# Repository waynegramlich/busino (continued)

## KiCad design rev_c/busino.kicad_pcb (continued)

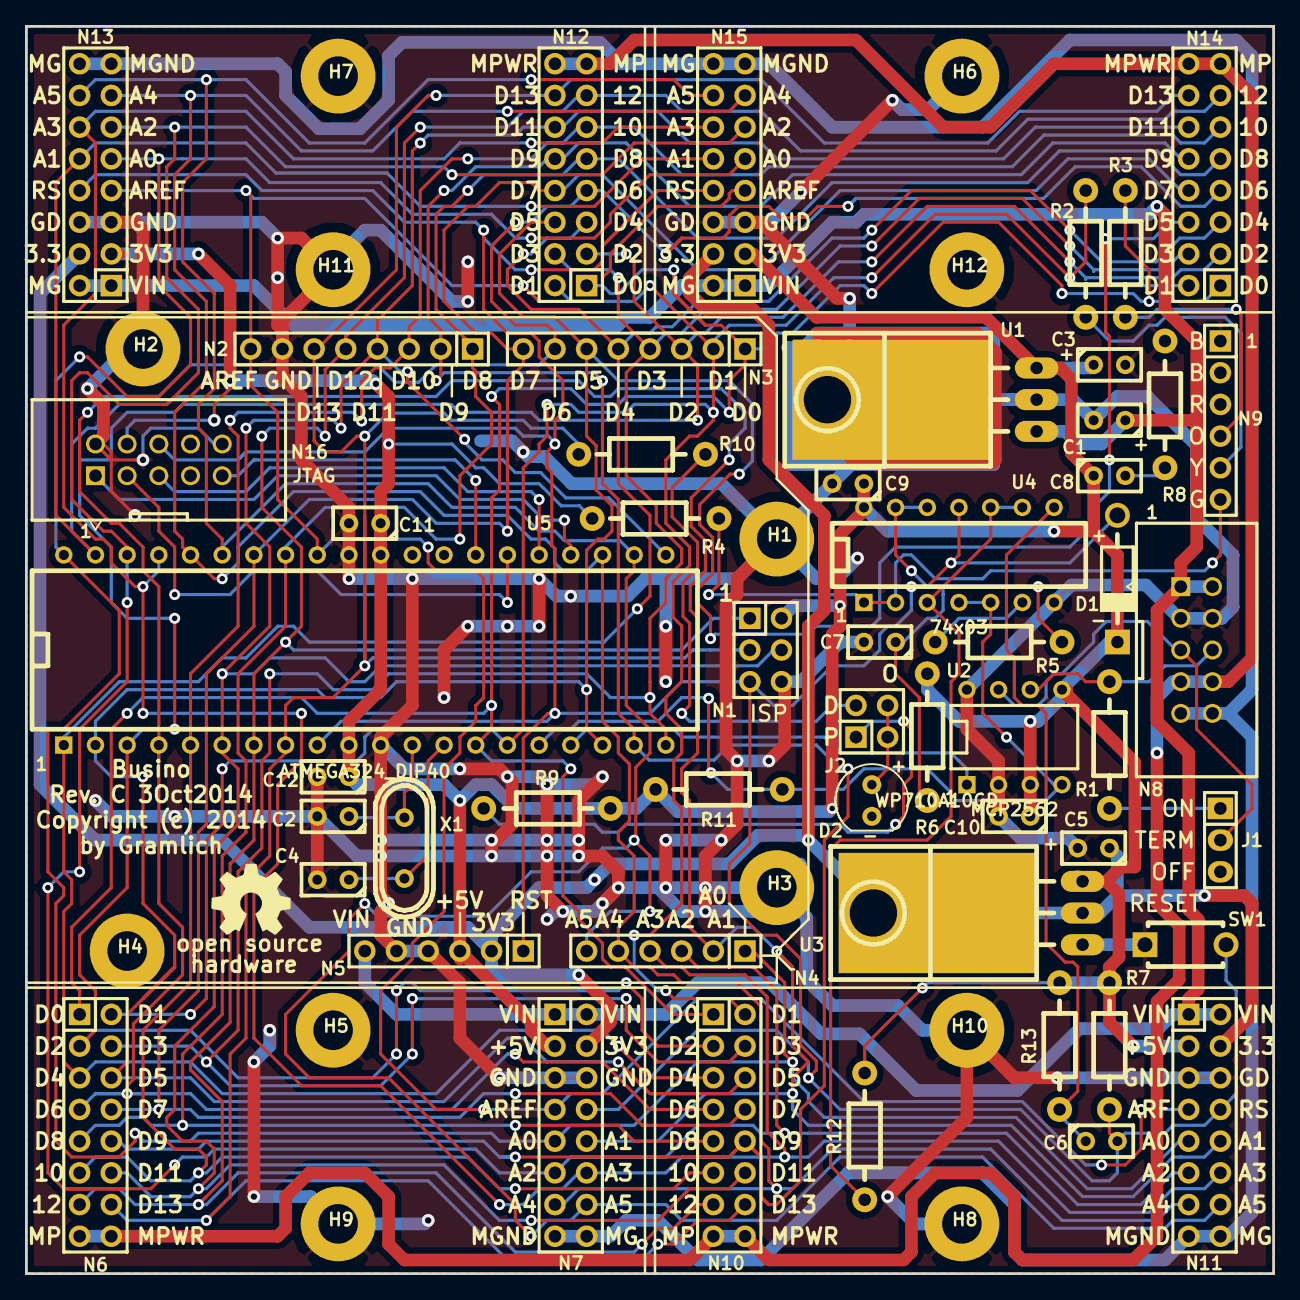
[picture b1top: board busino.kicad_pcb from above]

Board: 2 copper layers, 100.0 x 100.0 mm, 65 parts (0 on the bottom side), 50 nets.

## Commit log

2014-06-07 Initial files checked in.
2014-06-07 More work on processor schematic.
2014-06-07 Missed busino.dcm
2014-06-07 Added some more symbols to library.
2014-06-09 Making progress on processor sheet.
2014-06-14 Initial mounting hole layout is done.
2014-06-19 Worked on board.
2014-06-23 Busino passes DRC.
2014-06-23 Added more silk screen labels.
2014-07-09 Rev. A of the Busino board layout is in pretty good shape.
2014-07-13 Minor polishing. Noticed that mounting holes were masked when they should not be masked.
2014-07-13 More work on the ground plane.
2014-07-28 Made a clone of Rev. A.
2014-07-28 Switched libraries to use Rev. B libraries.
2014-07-31 Add in some derived files.
2014-08-14 Improved schematic description. Added missiong wire from processor pin 21 to pin 6.
2014-10-04 Minor changes to Rev. B prior to cloning for Rev. C.
2014-10-04 Did a clone of Rev. B into Rev. C.
2014-10-04 Rev. C is pretty much ready to go.
2014-10-20 Forgot to wrap up revisiton C.
